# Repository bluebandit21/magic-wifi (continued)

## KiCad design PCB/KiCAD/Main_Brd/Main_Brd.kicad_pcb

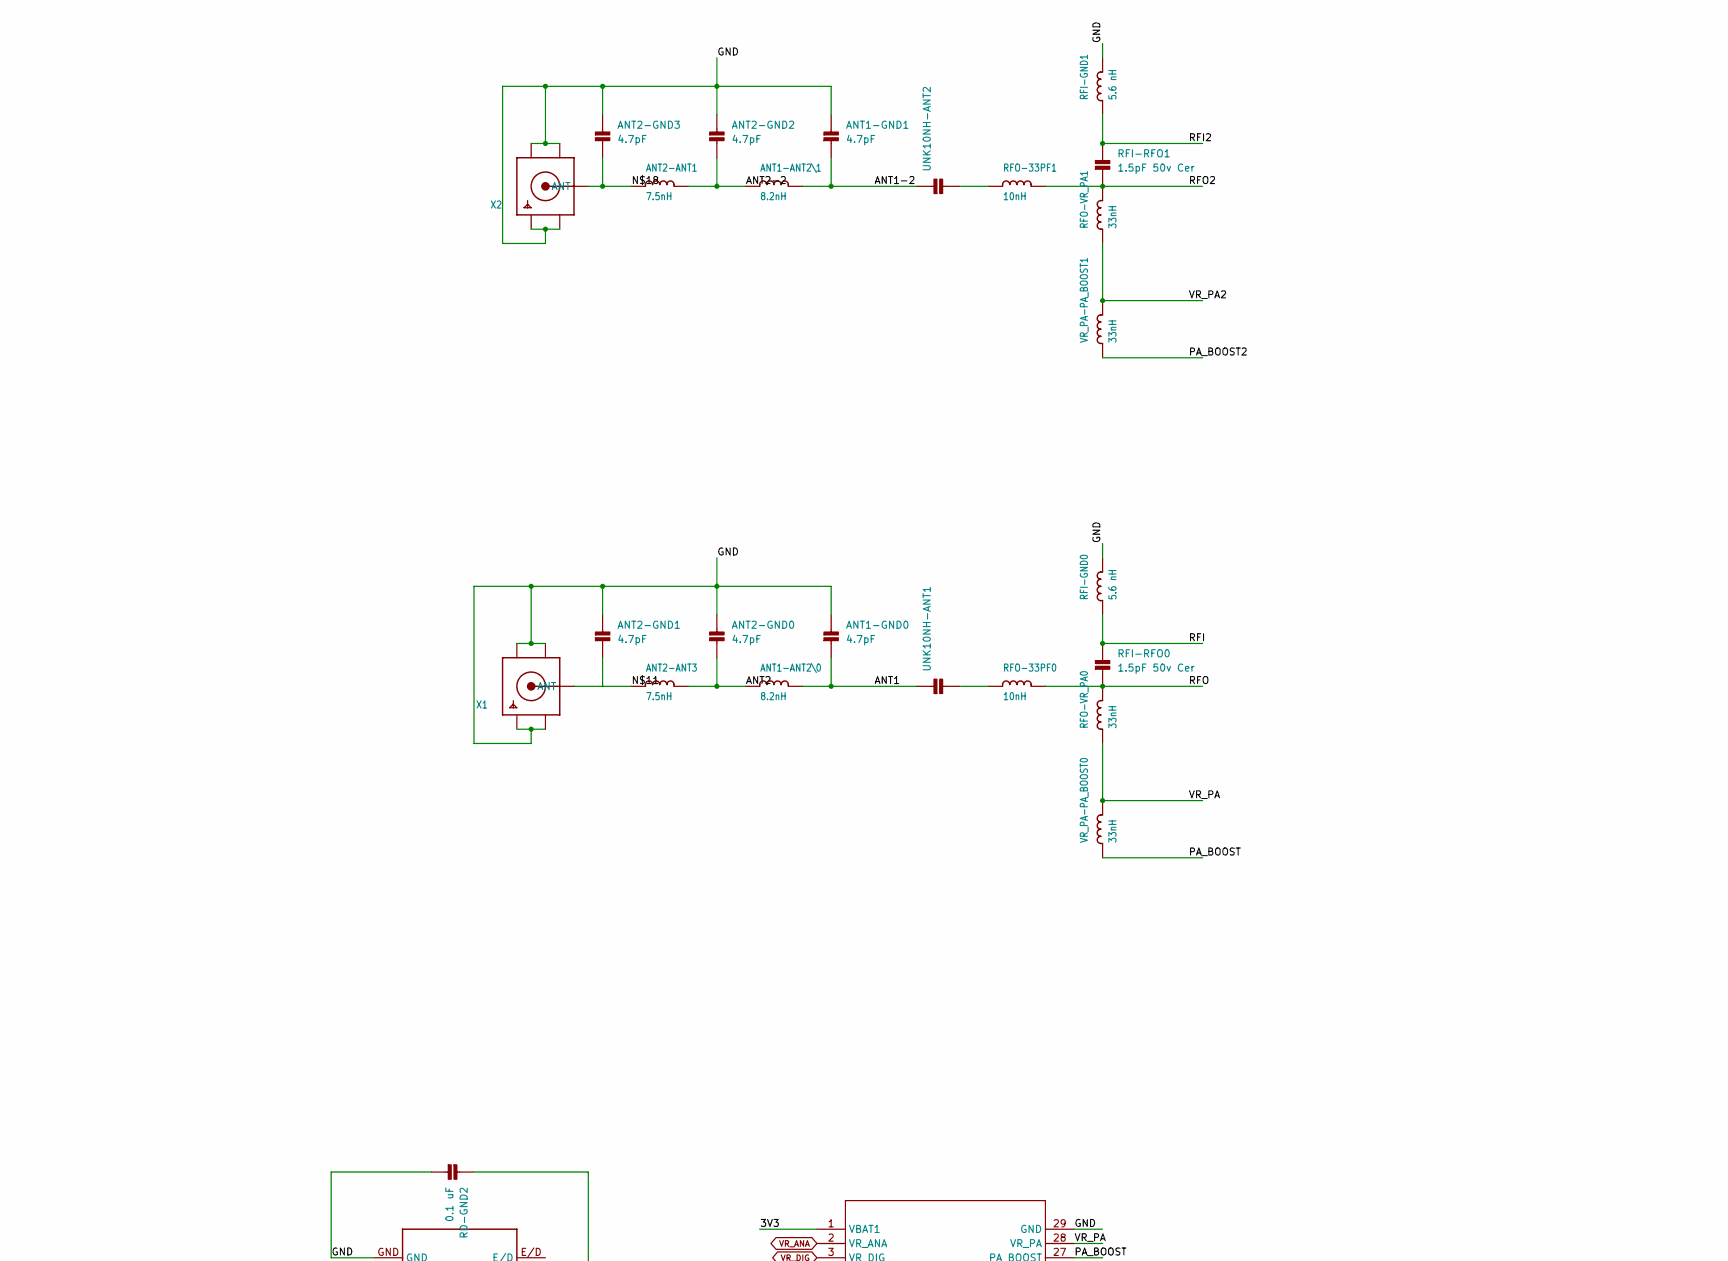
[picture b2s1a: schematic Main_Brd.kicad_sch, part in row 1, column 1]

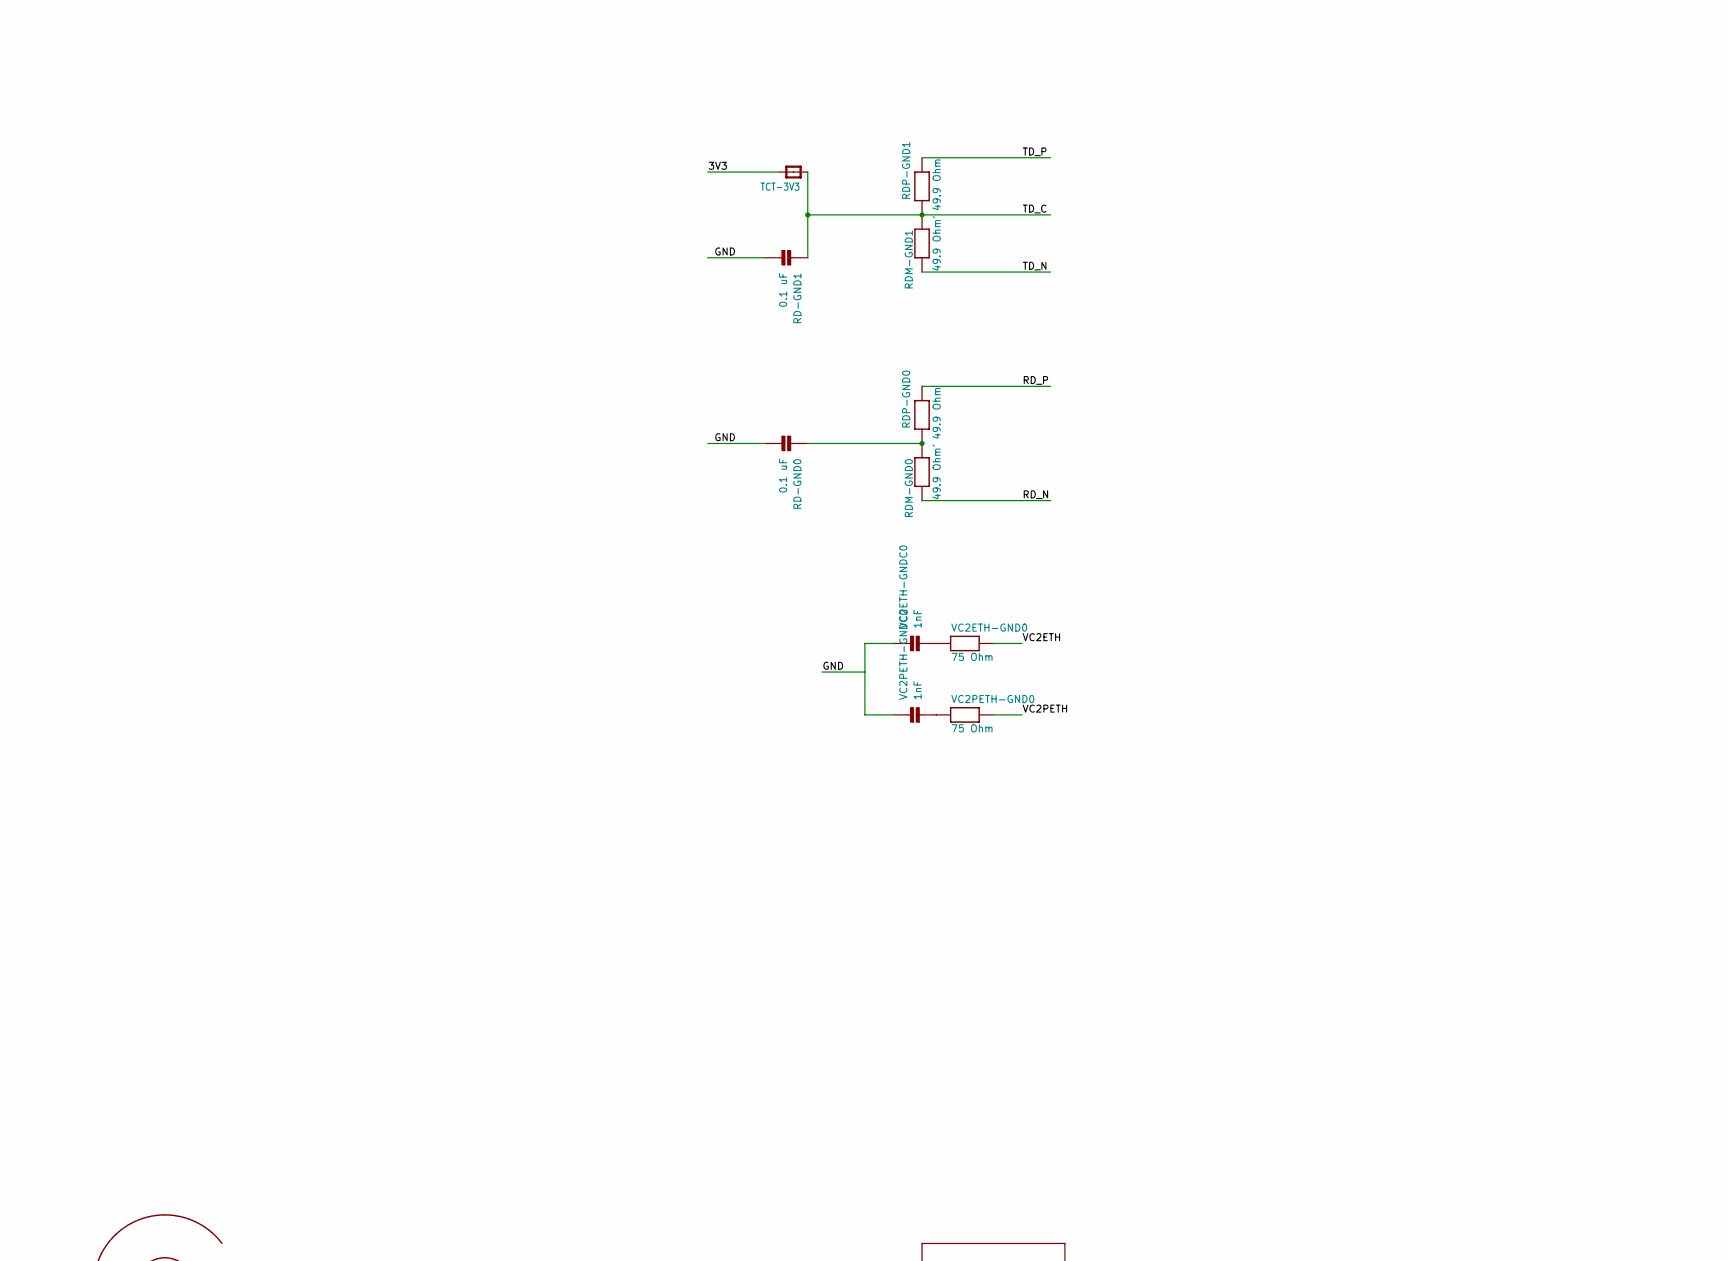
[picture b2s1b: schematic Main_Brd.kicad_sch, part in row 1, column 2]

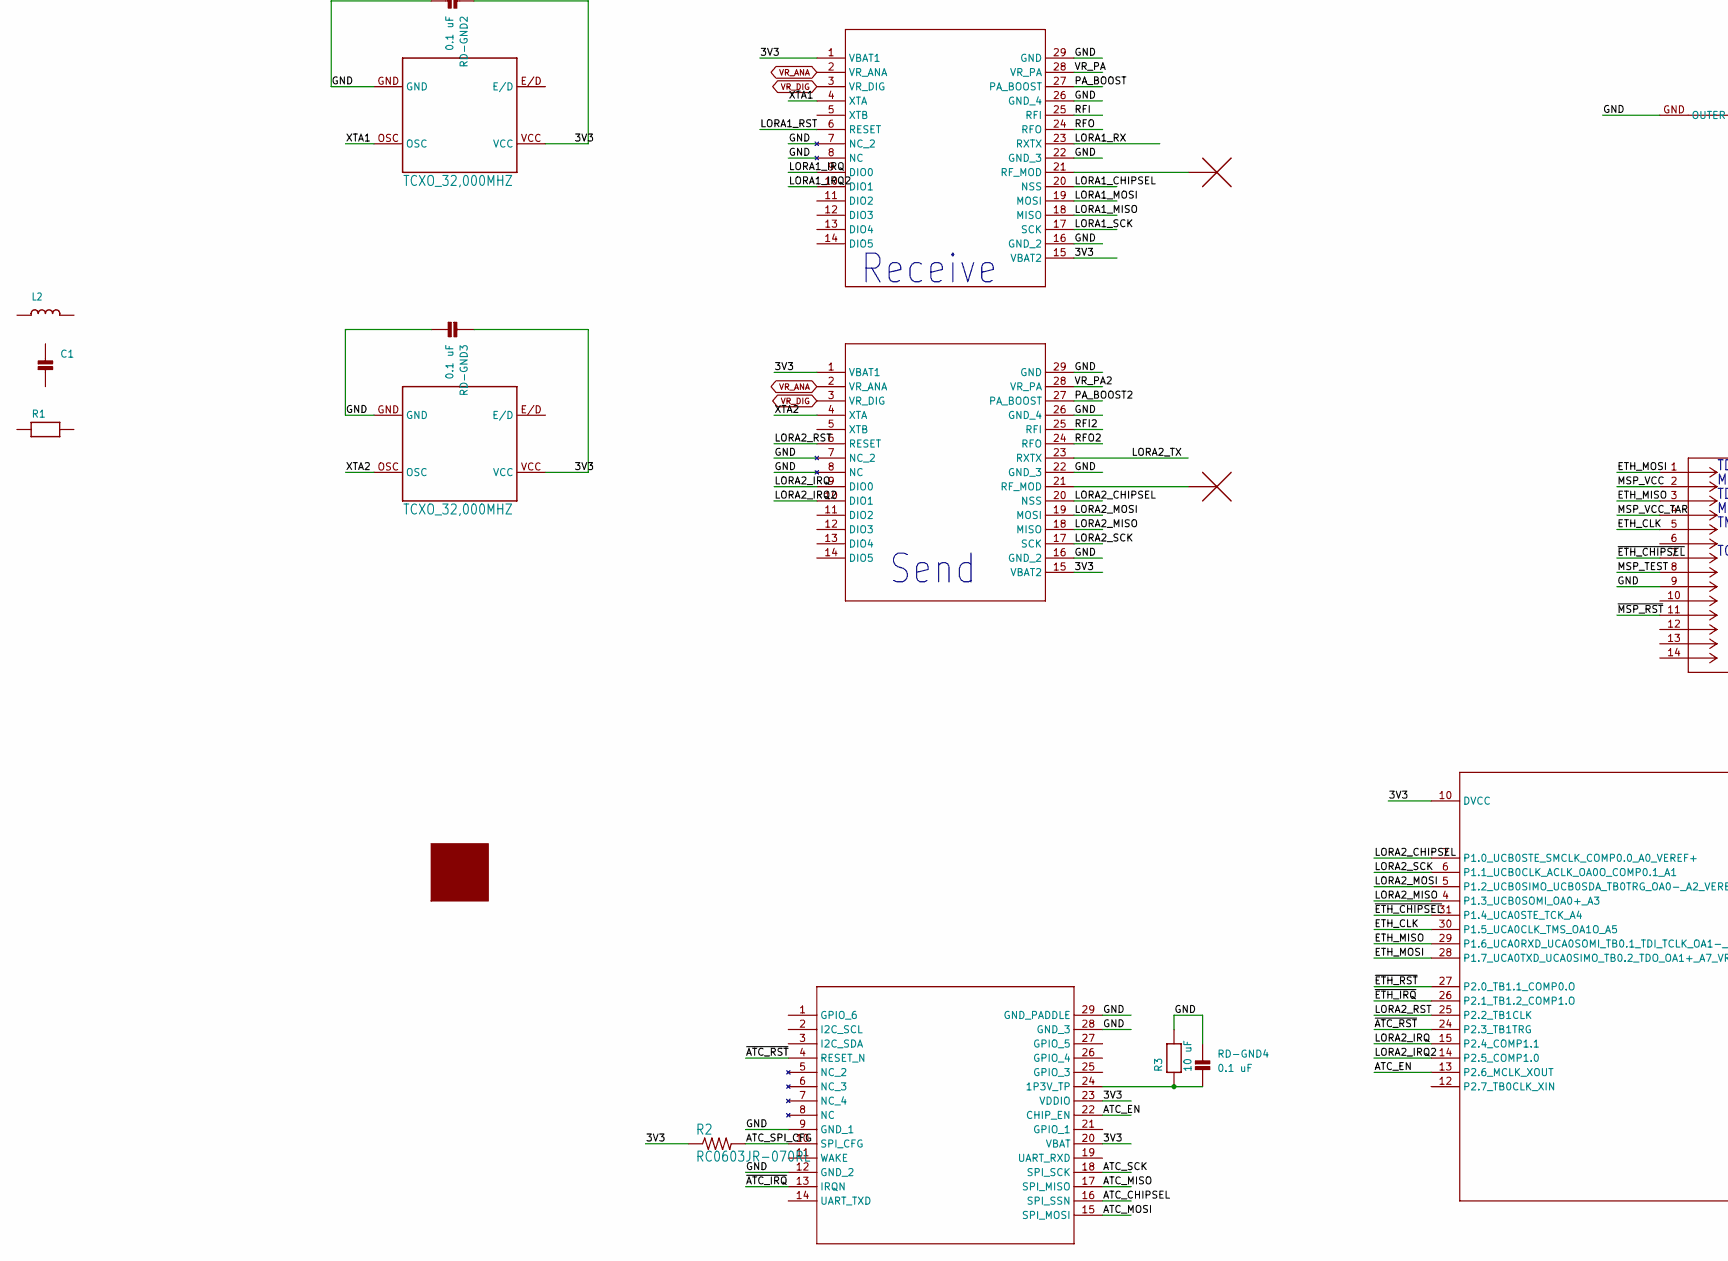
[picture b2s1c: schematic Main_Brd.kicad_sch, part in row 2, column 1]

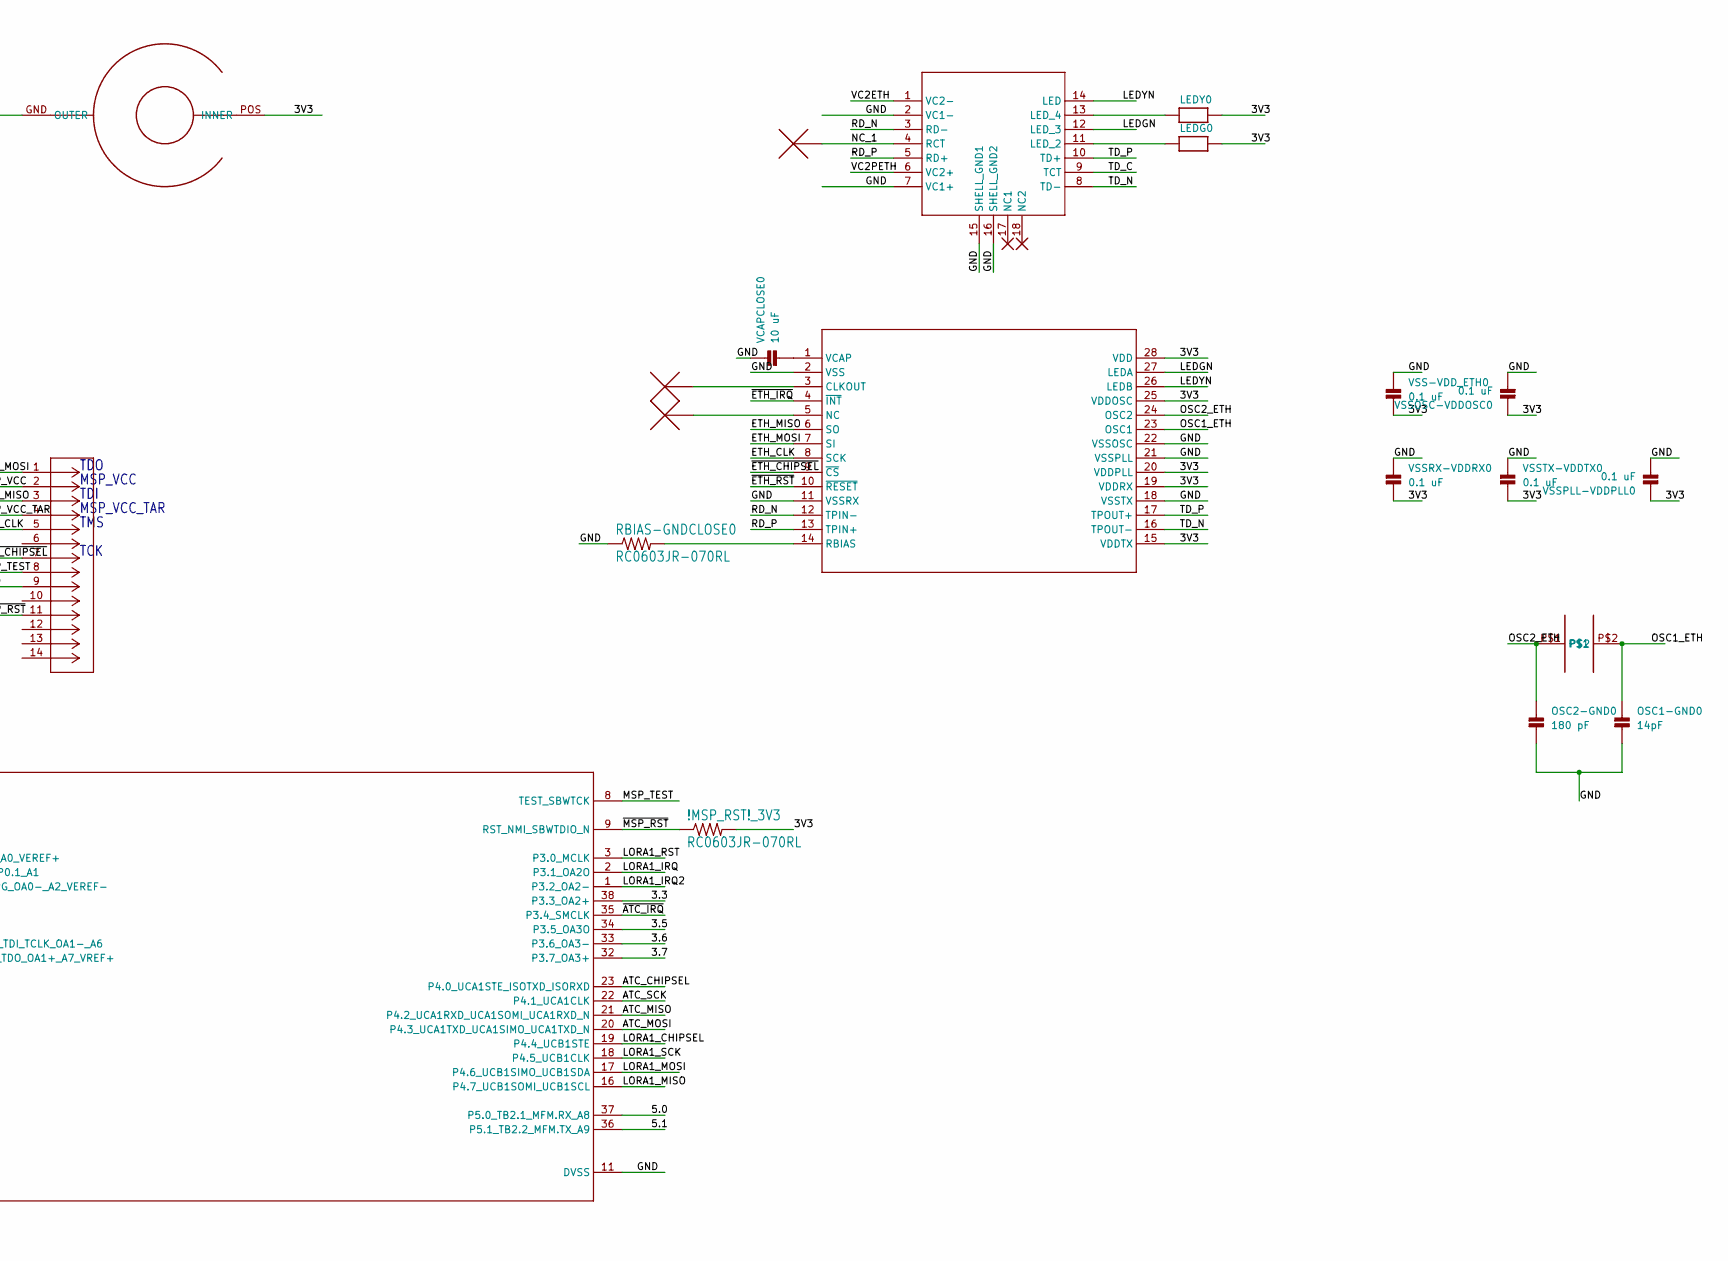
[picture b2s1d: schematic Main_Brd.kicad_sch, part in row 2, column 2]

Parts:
!MSP_RST!_3V3: RC0603JR-070RL; RES_0603
ANT1-ANT2\0, ANT1-ANT2\1: 8.2nH; _0402
ANT1-GND0, ANT1-GND1, ANT2-GND0, ANT2-GND1, ANT2-GND2, ANT2-GND3: 4.7pF; 0402
ANT2-ANT1, ANT2-ANT3: 7.5nH; _0402
C1: CAP_CERAMIC0402; 0402
ETH0: ENC28J60-I/SP; SPDIP28_300MC_MCH
L2: INDUCTOR_0402; _0402
LEDG0: RESISTOR0402; 0402
LEDY0: RESISTOR0402; 0402
LORA1, LORA2: SX1272IMLTRT; QFN28_6X6_SEM
OSC1-GND0: 14pF; 0603
OSC2-GND0: 180 pF; 0603
R1: RESISTOR0402; 0402
R2: RC0603JR-070RL; RES_0603
R3: 10 uF; _0805
RBIAS-GNDCLOSE0: RC0603JR-070RL; RES_0603
RD-GND0, RD-GND1, RD-GND2, RD-GND3, RD-GND4: 0.1 uF; 0603
RDM-GND0, RDM-GND1: 49.9 Ohm'; 0402
RDP-GND0, RDP-GND1: 49.9 Ohm; 0402
RFI-GND0, RFI-GND1: 5.6 nH; _0402
RFI-RFO0, RFI-RFO1: 1.5pF 50v Cer; 0402
RFO-33PF0, RFO-33PF1: 10nH; _0402
RFO-VR_PA0, RFO-VR_PA1: 33nH; _0402
TCT-3V3: FERRITE; 0603
TCXO1, TCXO2: TCXO_32,000MHZ; TCXO
TI-JTAG0: 702461401; CON_702461401_MOL
U1: ATWINC1500-MR210PB1952-T; ATWINC15X0-MR210_MCH
U3: MSP430FR2355TDBTRDBT0038A_M; DBT0038A_M
U6: ARJM11C7-114-BA-EW2; ARJM11C7-114-BA-EW2_ABR
U$2: J49SMH-P-G-G-K-25M0; 2PAD-11.5X4.8
U$7: BARREL_CONN_EXTERN
U$8: MAGICWIFI_X10; LOGOX10
UNK10NH-ANT1, UNK10NH-ANT2: CAP_CERAMIC0402; 0402
VC2ETH-GND0, VC2PETH-GND0: 75 Ohm; 0402
VC2ETH-GNDC0, VC2PETH-GNDC0: 1nF; 0402
VCAPCLOSE0: 10 uF; 0805
VR_PA-PA_BOOST0, VR_PA-PA_BOOST1: 33nH; _0402
VSS-VDD_ETH0: 0.1 uF; 0603
VSSOSC-VDDOSC0: 0.1 uF; 0603
VSSPLL-VDDPLL0: 0.1 uF; 0603
VSSRX-VDDRX0: 0.1 uF; 0603
VSSTX-VDDTX0: 0.1 uF; 0603
X1, X2: SMACONNECTOR_EDGE; SMA_EDGELAUNCH

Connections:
3.3: U3.38 (P3.3_OA2+)
3.5: U3.34 (P3.5_OA3O)
3.6: U3.33 (P3.6_OA3-)
3.7: U3.32 (P3.7_OA3+)
3V3: !MSP_RST!_3V3.2, ETH0.15 (VDDTX), ETH0.19 (VDDRX), ETH0.20 (VDDPLL), ETH0.25 (VDDOSC), ETH0.28 (VDD), LEDG0.2, LEDY0.2, LORA1.1 (VBAT1), LORA1.15 (VBAT2), LORA2.1 (VBAT1), LORA2.15 (VBAT2), R2.1, RD-GND2.1, RD-GND3.1, TCT-3V3.2, TCXO1.VCC, TCXO2.VCC, U1.20 (VBAT), U1.23 (VDDIO), U3.10 (DVCC), U$7.POS (INNER), VSS-VDD_ETH0.2, VSSOSC-VDDOSC0.1, VSSPLL-VDDPLL0.1, VSSRX-VDDRX0.2, VSSTX-VDDTX0.2
5.0: U3.37 (P5.0_TB2.1_MFM.RX_A8)
5.1: U3.36 (P5.1_TB2.2_MFM.TX_A9)
ANT1: ANT1-ANT2\0.2, ANT1-GND0.2, UNK10NH-ANT1.1
ANT1-2: ANT1-ANT2\1.2, ANT1-GND1.2, UNK10NH-ANT2.1
ANT2: ANT1-ANT2\0.1, ANT2-ANT3.2, ANT2-GND0.2
ANT2-2: ANT1-ANT2\1.1, ANT2-ANT1.2, ANT2-GND2.2
ATC_CHIPSEL: U1.16 (SPI_SSN), U3.23 (P4.0_UCA1STE_ISOTXD_ISORXD)
ATC_EN: U1.22 (CHIP_EN), U3.13 (P2.6_MCLK_XOUT)
ATC_MISO: U1.17 (SPI_MISO), U3.21 (P4.2_UCA1RXD_UCA1SOMI_UCA1RXD_N)
ATC_MOSI: U1.15 (SPI_MOSI), U3.20 (P4.3_UCA1TXD_UCA1SIMO_UCA1TXD_N)
ATC_SCK: U1.18 (SPI_SCK), U3.22 (P4.1_UCA1CLK)
ATC_SPI_CFG: R2.2, U1.10 (SPI_CFG)
ETH_CLK: ETH0.8 (SCK), TI-JTAG0.5, U3.30 (P1.5_UCA0CLK_TMS_OA1O_A5)
ETH_MISO: ETH0.6 (SO), TI-JTAG0.3, U3.29 (P1.6_UCA0RXD_UCA0SOMI_TB0.1_TDI_TCLK_OA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)
ETH_MOSI: ETH0.7 (SI), TI-JTAG0.1, U3.28 (P1.7_UCA0TXD_UCA0SIMO_TB0.2_TDO_OA1+_A7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)
GND: ANT1-GND0.1, ANT1-GND1.1, ANT2-GND0.1, ANT2-GND1.1, ANT2-GND2.1, ANT2-GND3.1, ETH0.2 (VSS), ETH0.11 (VSSRX), ETH0.18 (VSSTX), ETH0.21 (VSSPLL), ETH0.22 (VSSOSC), LORA1.7 (NC_2), LORA1.8 (NC), LORA1.16 (GND_2), LORA1.22 (GND_3), LORA1.26 (GND_4), LORA1.29 (GND), LORA2.7 (NC_2), LORA2.8 (NC), LORA2.16 (GND_2), LORA2.22 (GND_3), LORA2.26 (GND_4), LORA2.29 (GND), OSC1-GND0.2, OSC2-GND0.2, R3.2, RBIAS-GNDCLOSE0.1, RD-GND0.2, RD-GND1.2, RD-GND2.2, RD-GND3.2, RD-GND4.1, RFI-GND0.2, RFI-GND1.2, TCXO1.GND, TCXO2.GND, TI-JTAG0.9, U1.9 (GND_1), U1.12 (GND_2), U1.28 (GND_3), U1.29 (GND_PADDLE), U3.11 (DVSS), U6.2 (VC1-), U6.7 (VC1+), U6.15 (SHELL_GND1), U6.16 (SHELL_GND2), U$7.GND (OUTER), VC2ETH-GNDC0.1, VC2PETH-GNDC0.1, VCAPCLOSE0.1, VSS-VDD_ETH0.1, VSSOSC-VDDOSC0.2, VSSPLL-VDDPLL0.2, VSSRX-VDDRX0.1, VSSTX-VDDTX0.1, X1.GND@1 (GND4), X1.GND@2 (GND3), X1.GND@3 (GND2), X1.GND@4 (GND1), X2.GND@1 (GND4), X2.GND@2 (GND3), X2.GND@3 (GND2), X2.GND@4 (GND1)
LEDGN: ETH0.27 (LEDA), U6.12 (LED_3)
LEDYN: ETH0.26 (LEDB), U6.14 (LED)
LORA1_CHIPSEL: LORA1.20 (NSS), U3.19 (P4.4_UCB1STE)
LORA1_IRQ: LORA1.9 (DIO0), U3.2 (P3.1_OA2O)
LORA1_IRQ2: LORA1.10 (DIO1), U3.1 (P3.2_OA2-)
LORA1_MISO: LORA1.18 (MISO), U3.16 (P4.7_UCB1SOMI_UCB1SCL)
LORA1_MOSI: LORA1.19 (MOSI), U3.17 (P4.6_UCB1SIMO_UCB1SDA)
LORA1_RST: LORA1.6 (RESET), U3.3 (P3.0_MCLK)
LORA1_RX: LORA1.23 (RXTX)
LORA1_SCK: LORA1.17 (SCK), U3.18 (P4.5_UCB1CLK)
LORA2_CHIPSEL: LORA2.20 (NSS), U3.7 (P1.0_UCB0STE_SMCLK_COMP0.0_A0_VEREF+)
LORA2_IRQ: LORA2.9 (DIO0), U3.15 (P2.4_COMP1.1)
LORA2_IRQ2: LORA2.10 (DIO1), U3.14 (P2.5_COMP1.0)
LORA2_MISO: LORA2.18 (MISO), U3.4 (P1.3_UCB0SOMI_OA0+_A3)
LORA2_MOSI: LORA2.19 (MOSI), U3.5 (P1.2_UCB0SIMO_UCB0SDA_TB0TRG_OA0-_A2_VE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)
LORA2_RST: LORA2.6 (RESET), U3.25 (P2.2_TB1CLK)
LORA2_SCK: LORA2.17 (SCK), U3.6 (P1.1_UCB0CLK_ACLK_OA0O_COMP0.1_A1)
LORA2_TX: LORA2.23 (RXTX)
MSP_TEST: TI-JTAG0.8, U3.8 (TEST_SBWTCK)
MSP_VCC: TI-JTAG0.2
MSP_VCC_TAR: TI-JTAG0.4
unnamed: RFO-33PF0.1, UNK10NH-ANT1.2
unnamed: RFO-33PF1.1, UNK10NH-ANT2.2
unnamed: ETH0.1 (VCAP), VCAPCLOSE0.2
unnamed: VC2ETH-GND0.1, VC2ETH-GNDC0.2
unnamed: VC2PETH-GND0.1, VC2PETH-GNDC0.2
unnamed: LEDY0.1, U6.13 (LED_4)
unnamed: RD-GND0.1, RDM-GND0.1, RDP-GND0.1
unnamed: LEDG0.1, U6.11 (LED_2)
unnamed: ETH0.14 (RBIAS), RBIAS-GNDCLOSE0.2
unnamed: ANT2-ANT3.1, ANT2-GND1.2, X1.P (ANT)
unnamed: R3.1, RD-GND4.2, U1.24 (1P3V_TP)
unnamed: ANT2-ANT1.1, ANT2-GND3.2, X2.P (ANT)
OSC1_ETH: ETH0.23 (OSC1), OSC1-GND0.1, U$2.P$2
OSC2_ETH: ETH0.24 (OSC2), OSC2-GND0.1, U$2.P$1
PA_BOOST: LORA1.27 (PA_BOOST), VR_PA-PA_BOOST0.1
PA_BOOST2: LORA2.27 (PA_BOOST), VR_PA-PA_BOOST1.1
RD_N: ETH0.12 (TPIN-), RDM-GND0.2, U6.3 (RD-)
RD_P: ETH0.13 (TPIN+), RDP-GND0.2, U6.5 (RD+)
RFI: LORA1.25 (RFI), RFI-GND0.1, RFI-RFO0.1
RFI2: LORA2.25 (RFI), RFI-GND1.1, RFI-RFO1.1
RFO: LORA1.24 (RFO), RFI-RFO0.2, RFO-33PF0.2, RFO-VR_PA0.2
RFO2: LORA2.24 (RFO), RFI-RFO1.2, RFO-33PF1.2, RFO-VR_PA1.2
TD_C: RD-GND1.1, RDM-GND1.1, RDP-GND1.1, TCT-3V3.1, U6.9 (TCT)
TD_N: ETH0.16 (TPOUT-), RDM-GND1.2, U6.8 (TD-)
TD_P: ETH0.17 (TPOUT+), RDP-GND1.2, U6.10 (TD+)
VC2ETH: U6.1 (VC2-), VC2ETH-GND0.2
VC2PETH: U6.6 (VC2+), VC2PETH-GND0.2
VR_ANA: LORA1.2 (VR_ANA), LORA2.2 (VR_ANA)
VR_DIG: LORA1.3 (VR_DIG), LORA2.3 (VR_DIG)
VR_PA: LORA1.28 (VR_PA), RFO-VR_PA0.1, VR_PA-PA_BOOST0.2
VR_PA2: LORA2.28 (VR_PA), RFO-VR_PA1.1, VR_PA-PA_BOOST1.2
XTA1: LORA1.4 (XTA), TCXO1.OSC
XTA2: LORA2.4 (XTA), TCXO2.OSC
~ATC_IRQ: U1.13 (IRQN), U3.35 (P3.4_SMCLK)
~ATC_RST: U1.4 (RESET_N), U3.24 (P2.3_TB1TRG)
~ETH_CHIPSEL: ETH0.9 (~CS), TI-JTAG0.7, U3.31 (P1.4_UCA0STE_TCK_A4)
~ETH_IRQ: ETH0.4 (~INT), U3.26 (P2.1_TB1.2_COMP1.O)
~ETH_RST: ETH0.10 (~RESET), U3.27 (P2.0_TB1.1_COMP0.O)
~MSP_RST: !MSP_RST!_3V3.1, TI-JTAG0.11, U3.9 (RST_NMI_SBWTDIO_N)

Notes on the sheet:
MSP_VCC
TMS
TDI
Send
MSP_VCC_TAR
TCK
Receive
TDO

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
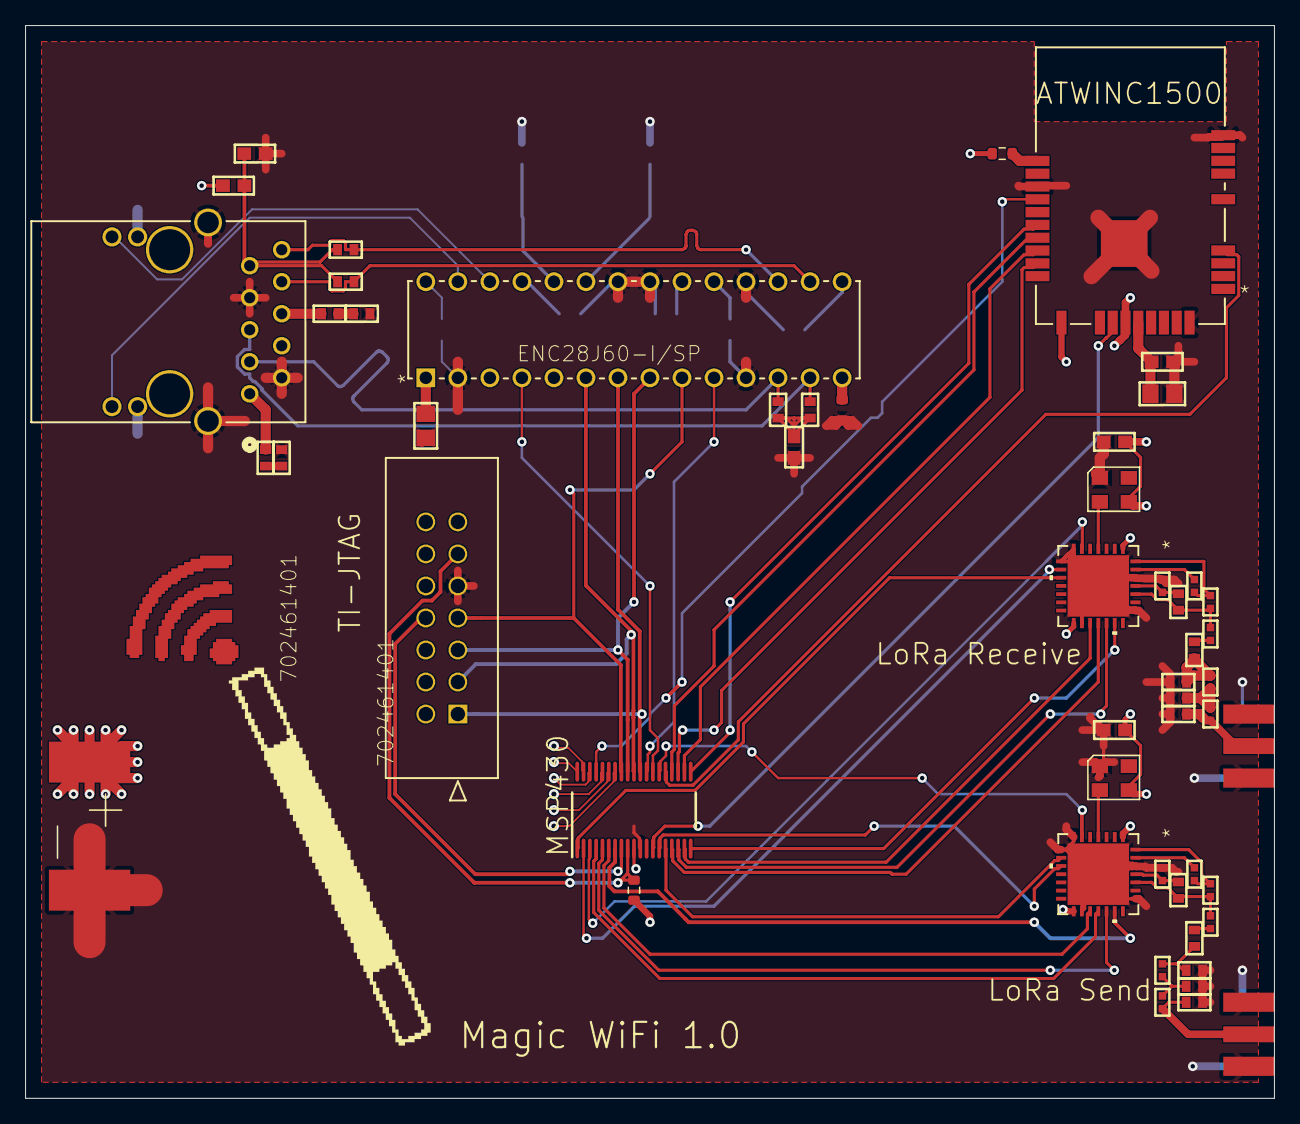
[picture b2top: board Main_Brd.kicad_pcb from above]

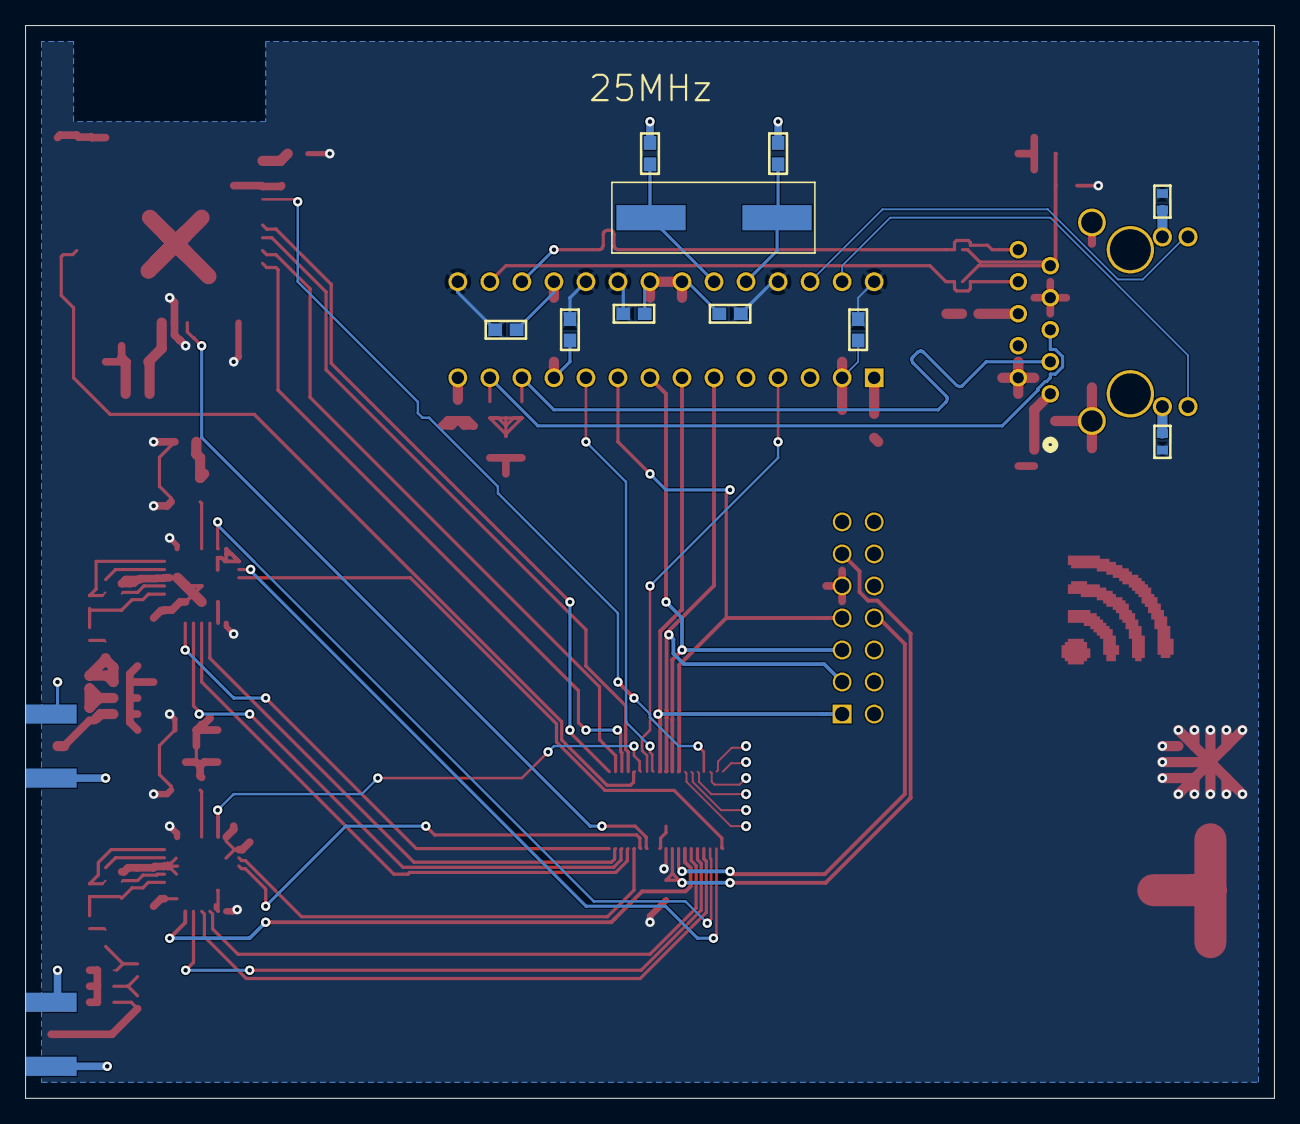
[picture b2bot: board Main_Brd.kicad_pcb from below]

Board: 2 copper layers, 99.1 x 85.1 mm, 64 parts (10 on the bottom side), 71 nets.

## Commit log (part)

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2022-09-22 pcb folder added
2022-10-05 Added gitignore and wildcards
2022-10-05 PCB starting push
2022-10-05 renamed md file for git recognition
2022-10-05 Added code owners
2022-10-07 LoRa Antenna + Ethernet routing
2022-10-07 Grab latest release (Version 1.1.0) of EtherCard as starting base
2022-10-07 Simple description of purpose of Dev/ directory
2022-10-07 Add in simple code for sending out raw frame
2022-10-11 Rename DEV.md to README.md
2022-10-13 Copy ported driverlib over to dev/ directory
    It originated from the freertos-port branch, commit 4cc4d2325960996544997719645f41739cafa460
2022-10-13 Draft of driver file
    Removed Debug
2022-10-17 Fixed minor bugs in port
2022-10-17 added eth power coupling and Osc circuit
2022-10-17 removed LED group
2022-10-17 adjusted crystal oscillator values
2022-10-18 compiles, fixed minor issue
2022-10-18 Antenna's Arranged
2022-10-18 edited ethernet with minor routing
2022-10-19 new oscillator added into circuit
2022-10-19 moved 3V3
2022-10-19 Added Ethernet
2022-10-19 added JTAG Port
2022-10-20 Added more custom libraries
2022-10-20 placed JTAG Port
2022-10-23 First iteration, working full library, not just driver, both Tx/Rx
2022-10-24 added wire labels
2022-10-27 Working blink LED example (full demo doesn't run yet)
2022-10-27 Added gitignore to ignore Debug stuff
2022-10-27 SPI example works up to 24MHz (so far)
2022-10-27 Minimizing FreeRTOS project files
2022-10-27 16M MCLK and 8M SMCLK, Deferred Interrupt works on RTOS
2022-10-27 Working deferred interrupt example with P4.1 button
2022-10-27 Fixed SPI clockPhase value according to ENC driver
2022-10-27 Untracked .settings and targetConfigs and added them to gitignore
2022-10-28 Duplicate EtherCard, ENC28J60 Arduino test in order to begin minimization
    Before porting EtherCard, we will remove all of the (very large amount) of
    functionality present that we won't actually need.
    Not having to port over any of the TCP/UDP stack, DNS, DHCP, web stuff, etc...
    will make the process dramatically simpler.
2022-10-28 Begin removing large amounts of code from EtherCard
2022-10-28 Continue ripping out large swathes of functionality
2022-10-28 Create initial framework for attempting to port EtherCard to MSP430FR2355
2022-10-28 Port SPI-related Arduino functions over to MSP430
    This commit compiles but does not work correctly, investigation shows that
    SPI is not behaving as intended and chip select is the likely culprit.
2022-10-28 Replace Arduino pin IO with driverlib equivalent:
    Note: SPI Ports+Pins not yet assigned!
2022-10-28 MSP430 Sends Working Ethernet Frames!
    A few issues fixed by this commit:
    1) It turns out the chip select is actually super important for signalling
    and can't just be tied to ground -- this adds in logic for properly setting
    and unsetting it.
    2) The settings used for SPI assumed data was transferred on the falling
    edge of the clock, which is not the case. This commit fixes that behavior.
2022-10-28 Added reset and cs config
2022-10-28 All Passives Complete
2022-10-28 readable excel of SPI Ports
2022-10-28 Remove travis CI files that accidentally got copied when porting EtherCard
    Because they were hidden files, they managed to avoid me when I removed all of
    the other random non-applicable files a while back.
2022-10-28 more traces ran, ENC, JTAG
2022-10-29 Added interrupts, need more testing
2022-10-31 Debugged interrupts
2022-10-31 Added first instance of class to handle the subframes
2022-11-01 pcb moving forward
2022-11-01 WIP working on bus wrapper
2022-11-02 added barrel connector
2022-11-02 added keepout
2022-11-02 WIP porting Arduino Wifi101 over
2022-11-03 finished pcb v1
2022-11-03 Saving work at higher level in case we want to come back to it
2022-11-03 Got printf working, debugging SPI bus problem in read chip id
2022-11-03 Added debug ports
2022-11-04 Change EtherCard pinouts to use new select pin (P1.4 instead of P3.6)
2022-11-04 Create new CCS project for Ethernet LoRa integration testing
    Hopefully this works between computers, we will see.
2022-11-04 AP hosting works
2022-11-04 Move LoRa Driver and Subframe code into /dev folder
2022-11-04 Include LoRa drivers in Ethernet LoRa Integration Test Project
2022-11-04 Added Atmel examples full folders, added status LEDs
2022-11-06 Final Revision V1.1 for Print
2022-11-06 added photo for MSP Sch
2022-11-07 TEMP wip commit
2022-11-07 WIP vector changes
2022-11-07 BROKEN WIP
2022-11-07 WIP fixed interrupt, AP works but client does not do anything after connect()
2022-11-07 organized libraries
2022-11-08 Added TCP client and server examples
2022-11-09 Added SPI block receive buffer
2022-11-09 Added demo of Lora to Ethernet
2022-11-11 [[RENAME ME]] Horrifying C++ syntax to make multiple LoRa instances work
2022-11-11 Un global-ize things that should be member variables
    Done by pushing SX127x_driver function inside of SX127x class where
    they probably should have been the entire time.
2022-11-11 Remove no-longer existent file from CCS project
2022-11-11 (Not yet working) attempt at Ethernet receive -> Lora send pipeline
2022-11-11 Send/Recieve code both verified
2022-11-14 Fixed Rx Subframe Bugs
2022-11-14 Tom is dumb and put double #defines
2022-11-14 WIP AP receives weird packets that are not from client
2022-11-15 Added test class for frametranslater
2022-11-16 Layer 2 receive success with modified header
2022-11-17 Fixed a few minor bugs in FrameTranslater using the provided tests
2022-11-17 PCBV1.2 Gerbers
2022-11-18 Hacky fix for clock
    We discovered that despite the Ethernet intialization functions properly
    setting the SPI clock rate of the Ethernet to 8Mhz, the Lora initialization
    functions does *something* to the system clocks that happens to make the
    Ethernet SPI run at 24 Mhz...
    Unfortunately, the ENC28J60 is remarkably *almost* able to work properly at
    this speed, despite it being 3x the max, but the ways it doesn't work tend
2022-11-18 WIP tx/rx basic functions
2022-11-18 Other side
2022-11-18 Fix system clocks mostly in a less hacky way
    We set up the system clocks exactly *once* now, but as a consequence
    everything runs at 4 Mhz which is slightly suboptimal.
    We'll want to fix this better later.
2022-11-18 Set up rudimentary system for interrupt-based handling!
    Note: This currently has a very nasty potential race condition in it due
    to our lack of atomic operations:
    In check_set_eth_pending, if the interrupt line is high (inactive) when we
    call the GPIO function, then the function is pre-empted by the ISR for the Eth
    before we actually set the value, we will set eth_available to true before
    immediately changing it to false as we return into check_set_eth_pending.
2022-11-18 Change Ethernet frame sizes around appropriately
    The number 1518 was hard-coded in a few spots when it really should have been
    1514, as we don't include the 4 byte CRC.
    Additionally, we were invoking UB and possibly (realistically not,
    but theoretically) causing problems by consistently overreading past the end
    of our Ethernet array, this simply adds enough padding at the end (that will
    be full of random junk) that fixes our problem.
2022-11-18 Add delay in FrameTranslator send in between LoRa frames
    Otherwise, we think we might risk sending too fast by continuously sending
    resulting in the receiver falling behind if it's doing anything else at the
    time.
    More testing is required.
2022-11-18 Add in framework for non-blocking bidirectional communication
    This, unfortunately, does not fully work *quite* yet as the send/receive
    both currently share the same buffer, which is a problem as they ovewrite each
    other constantly.
2022-11-20 Begin reworking Ethernet send operations to faciliatate rx/tx blocking
2022-11-20 Correctly enable promiscuous mode on ENC28J60 to receive all traffic
    The subsequent calls to enable various receiving on the Ethernet had the side
    effect of *disabling* promiscuous mode.
    As a result, we dropped all unicast traffic instead of forwarding it along,
    causing very obvious problems in being able to send traffic end-to-end :)
    Just deleting the subsequent calls amusingly leaves us where we wanted to be,
    with us receiving absolutely everything.
2022-11-20 WIP Standardized AP and STA code, testing two-way comms
2022-11-20 WIP Removed printfs and made sure it compiles
2022-11-20 WIP same as above
2022-11-20 Two-way communication cont'd
2022-11-21 Fixed issue with GPIO unlock, moving PMM_unlockLPM5 to main where it belongs for reliable operation.
2022-11-21 WIP single-file defines-based solution
2022-11-21 Random comment test for cross-platform dev
2022-11-21 Remove many of the unwanted files from wifi-port branch
2022-11-21 Symbolically link ATWINC1500_MSP to match structure of other driver files
2022-11-21 Fixed ISRs
2022-11-21 Added Wifi init functions
2022-11-21 Can initialize Wifi
2022-11-22 Before integrating Wifi to Ethernet
2022-11-28 Update Ethernet MTU and buffer sizes in order to be able to hold 802.1Q tag
    Closes: #12
2022-11-28 Very WIP attempt at wifi integration
2022-11-28 Add in code for attempting to automatically reconnect wifi when disconnected
2022-11-28 Move FrameTranslater from stack to BSS to prevent stack overflow that led to memory corruption
    Because FrameTranslater holds an entire LoRa subframe, which is actually *quite* large, it led to us overflowing our stack and overwriting
    random low-level addresses with garbage, which led to crashes/generally bad behavior.
    By using placement new, this problem is fixed.
2022-11-29 Use stack size 300 and using 288, memory uncorrupted
2022-11-29 Fixed AP not hosting issue by un-reducing m2m types
2022-11-29 Fixed missing check_set_eth_pending in eth sending in wifi mode
2022-11-30 Fixed ether.sendPacket length bug
2022-11-30 Add TODO comments pointing out things to remove, fix reconnect counter
    Earlier, the reconnect coutner had a problem where if it passed 500 while the
    wifi was connected, it wouldn't attempt to reconnect after being disconnected
    until it overflowed the entirety of the uint16_t
2022-12-03 Remove ARP test frame as it is no longer needed
2022-12-03 Change timing of Ethernet reset
    Now we wait a bit with it held low and wait a bit afterwards so we don't
    immediately try to write any registers after the reset.
2022-12-03 Removed busy-waits from LoRa SPI
2022-12-03 Don't comment out wifi connection update in actual branch
2022-12-03 Hide SSID of network to hopefully prevent random people from connecting to it
2022-12-03 Add descriptive comment to initRTC function
2022-12-03 Added Wifi Enable line which must be high
2022-12-04 Add some hacky garbage to make defines.h C-compatible ish
2022-12-04 Change wifi reconnect attempt delay to use global timestamp system
2022-12-04 Preprocessor based version spoofing for PCB (19.5.x) wifi module
2022-12-04 fixup! Add disconnection timeout for BOARD_A
2022-12-04 Revert "Change wifi disconnection heartbeat method"
    This reverts commit 069bf0bbed9bc805b4859e840c03387d0ee79d31.
2022-12-04 Revert "fixup! Add disconnection timeout for BOARD_A"
    This reverts commit c66043d07f40b254e250381a7da3dff6d12c6575.
2022-12-05 Revert "Revert "Add disconnection timeout for BOARD_A""
    This reverts commit 01ea8daf19ac3ba954d313b5608a4c018c041b92.
2022-12-05 Revert "Revert "Change wifi disconnection heartbeat method""
    This reverts commit ac604d488055fa19557710299ae9ea82e28652d1.
2022-12-05 Add in logic for sending periodic heartbeat!
2022-12-05 Fix "Don't send heartbeat to host" check to account for wifi header size
2022-12-06 Add in priority-checking logic for 802.1Q + 802.1p tagging
2022-12-06 Added LoRa single sends
2022-12-06 Enable LoRa subframe optimization
    TODO: Fix initSend length
2022-12-06 Fixed bug with LoRa sends long
2022-12-07 Hacky firmware thingy
2022-12-08 Revert "Revert "Preprocessor based version spoofing for PCB (19.5.x) wifi module""
    This reverts commit a94d3fe1d441c2012b9c62692bb83cdcf8d667a2.
    This is objectively bad, but we'll have to stick with it for now since
    we managed to break our ATWINC1500 in the process of repeatedly desoldering/
    soldering it.
2023-05-18 EaglePCB Changes: - Converted 4 layer to 2 layer for cost savings - Removed Fiducials for simplicity - Switched MOSI/MISO on LoRa1 for correctness
2023-05-18 Converted Eagle to KiCAD
2023-05-18 starter libs for MW from scratch
2023-05-19 Base footprints and symbols for major parts added
2023-05-27 Added components
2023-05-27 gitignore remove backups
2024-01-08 part way through PCB design
2024-01-14 Changes to docs as requested
